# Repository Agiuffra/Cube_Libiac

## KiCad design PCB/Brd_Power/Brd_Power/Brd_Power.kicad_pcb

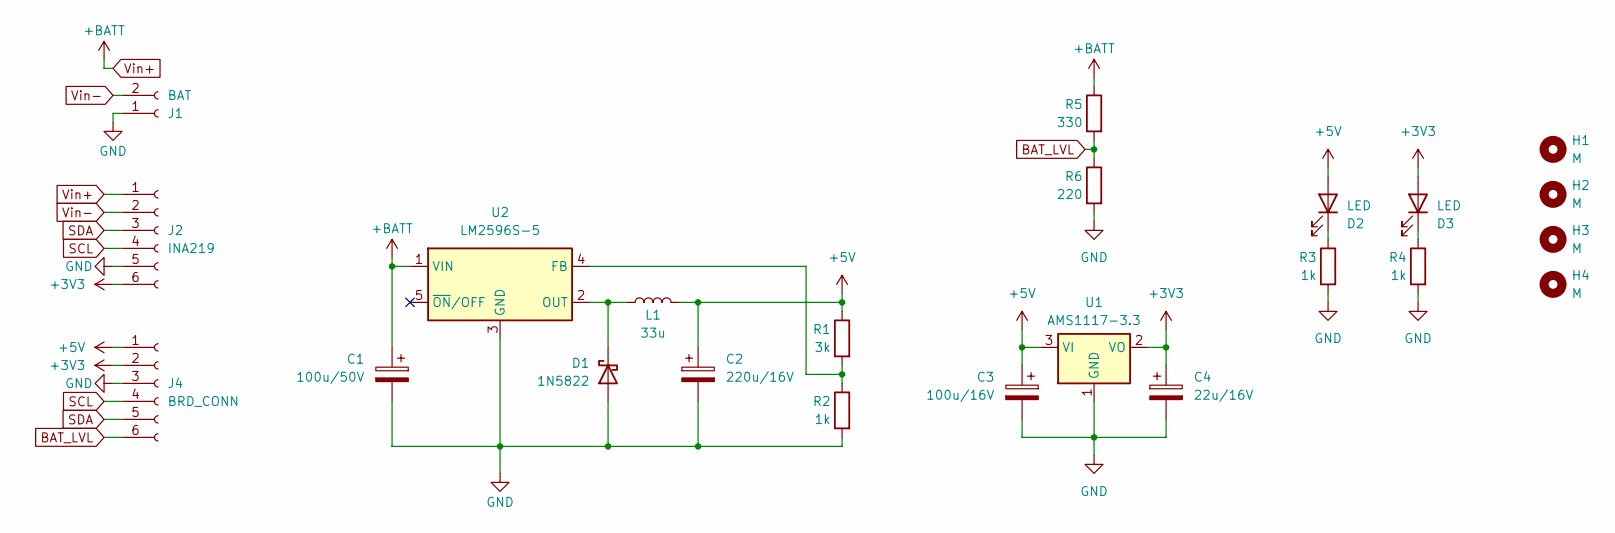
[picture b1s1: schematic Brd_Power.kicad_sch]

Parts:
C1: 100u/50V; CP_Elec_8x5.4
C2: 220u/16V; CP_Elec_8x5.4
C3: 100u/16V; CP_Radial_D6.3mm_P2.50mm
C4: 22u/16V; CP_Radial_D6.3mm_P2.50mm
D1: 1N5822; D_T-1_P5.08mm_Horizontal
D2, D3: LED; LED_D5.0mm_Horizontal_O1.27mm_Z3.0mm
H1, H2, H3, H4: M; MountingHole_3.2mm_M3_ISO14580
J1: BAT; Molex_KK-254_AE-6410-02A_1x02_P2.54mm_Vertical
J2: INA219; PinSocket_1x06_P2.54mm_Vertical
J4: BRD_CONN; PinHeader_1x06_P2.54mm_Vertical
L1: 33u; L_12x12mm_H8mm
R1: 3k; R_Axial_DIN0207_L6.3mm_D2.5mm_P2.54mm_Vertical
R2, R3, R4: 1k; R_Axial_DIN0207_L6.3mm_D2.5mm_P2.54mm_Vertical
R5: 330; R_Axial_DIN0207_L6.3mm_D2.5mm_P2.54mm_Vertical
R6: 220; R_Axial_DIN0207_L6.3mm_D2.5mm_P2.54mm_Vertical
U1: AMS1117-3.3; SOT-223-3_TabPin2
U2: LM2596S-5; TO-263-5_TabPin3

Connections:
+3V3: C4.1, D3.2 (A), J2.6, J4.2, U1.2 (VO)
+5V: C2.1, C3.1, D2.2 (A), J4.1, L1.2, R1.1, U1.3 (VI)
BAT_LVL: J4.6, R5.2, R6.1
GND: C1.2, C2.2, C3.2, C4.2, D1.2 (A), J1.1, J2.5, J4.3, R2.2, R3.2, R4.2, R6.2, U1.1 (GND), U2.3 (GND)
unnamed: D1.1 (K), L1.1, U2.2 (OUT)
unnamed: D2.1 (K), R3.1
unnamed: D3.1 (K), R4.1
unnamed: R1.2, R2.1, U2.4 (FB)
SCL: J2.4, J4.4
SDA: J2.3, J4.5
Vin+: C1.1, J2.1, R5.1, U2.1 (VIN)
Vin-: J1.2, J2.2

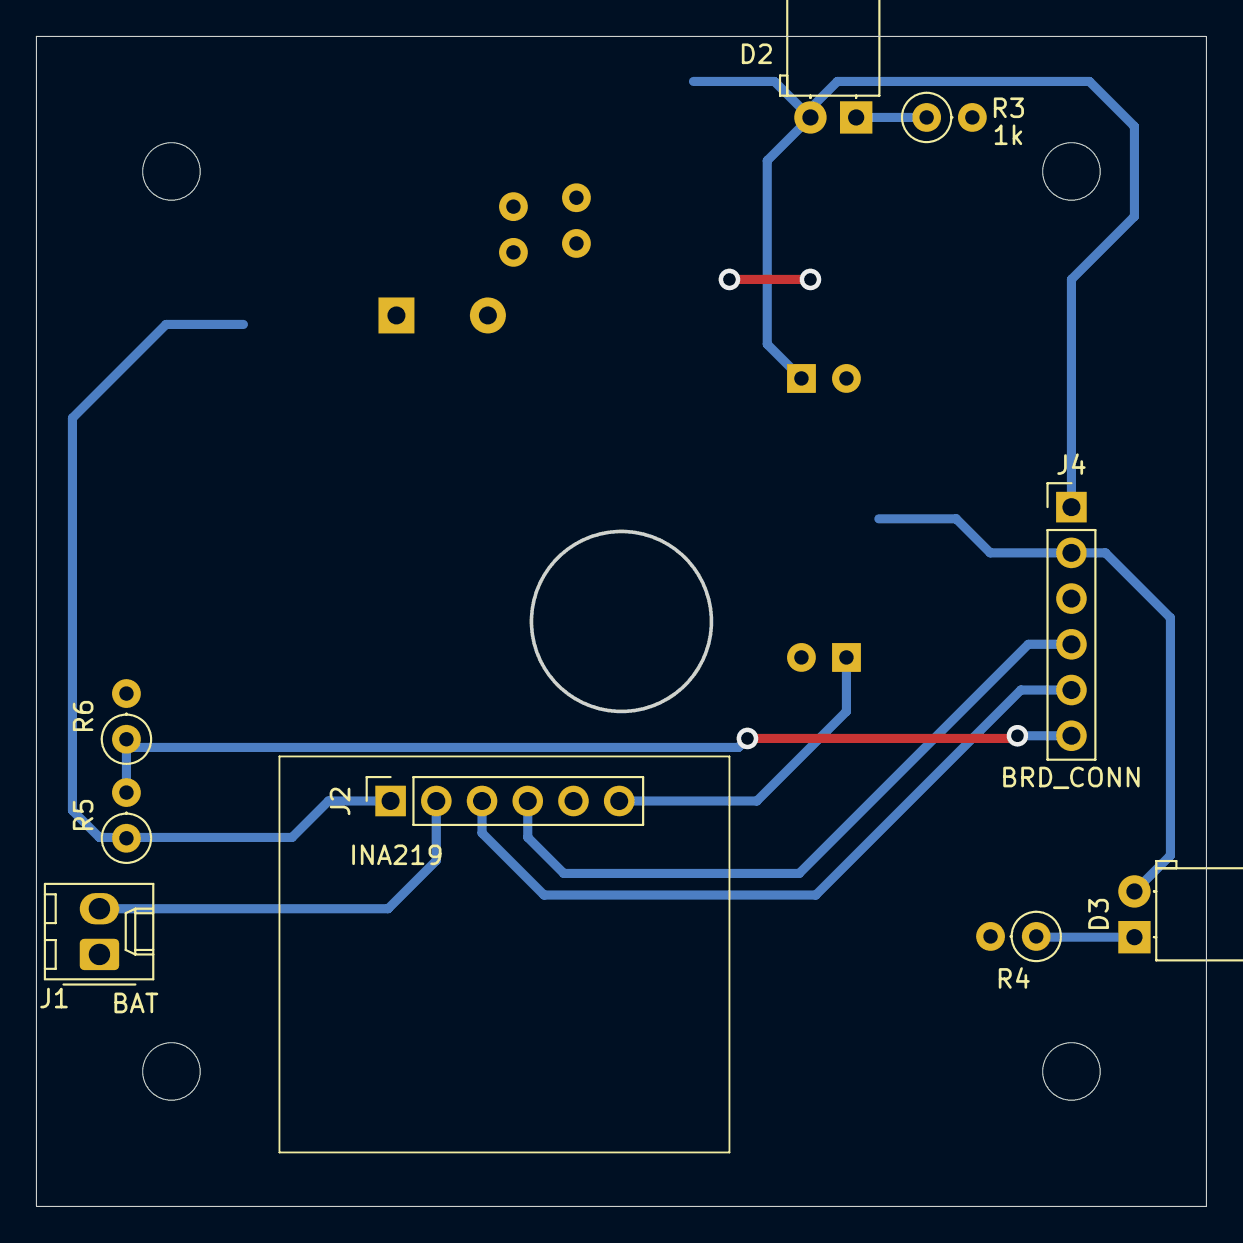
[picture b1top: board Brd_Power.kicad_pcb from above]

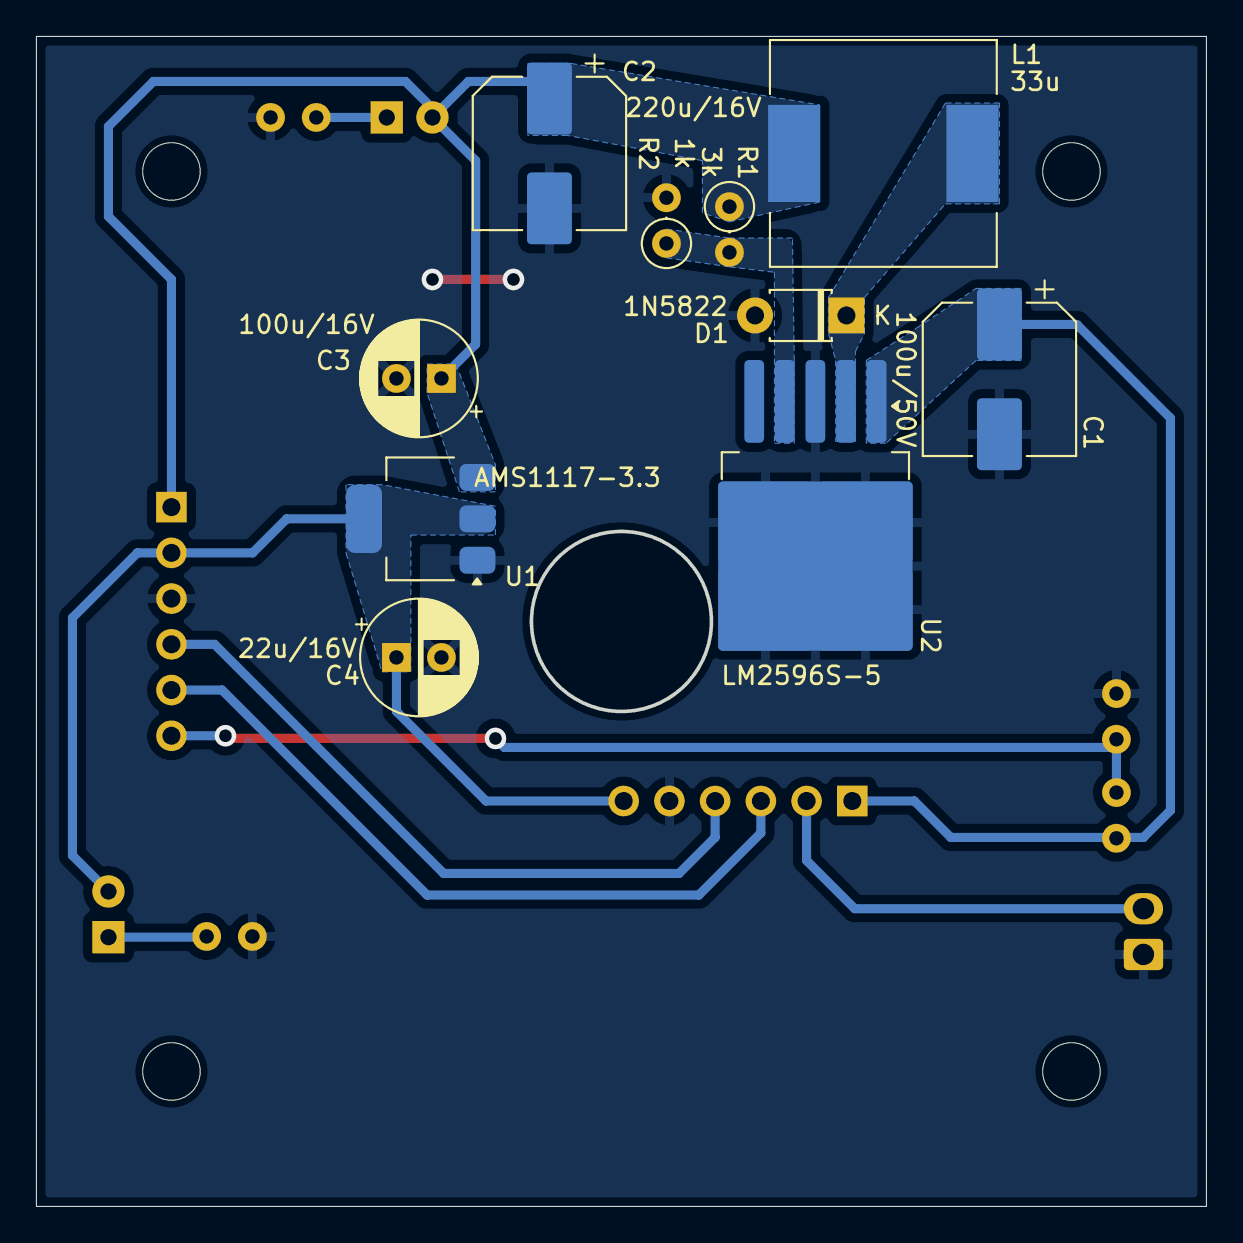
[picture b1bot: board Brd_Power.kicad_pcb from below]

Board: 2 copper layers, 65.0 x 65.0 mm, 23 parts (10 on the bottom side), 12 nets.

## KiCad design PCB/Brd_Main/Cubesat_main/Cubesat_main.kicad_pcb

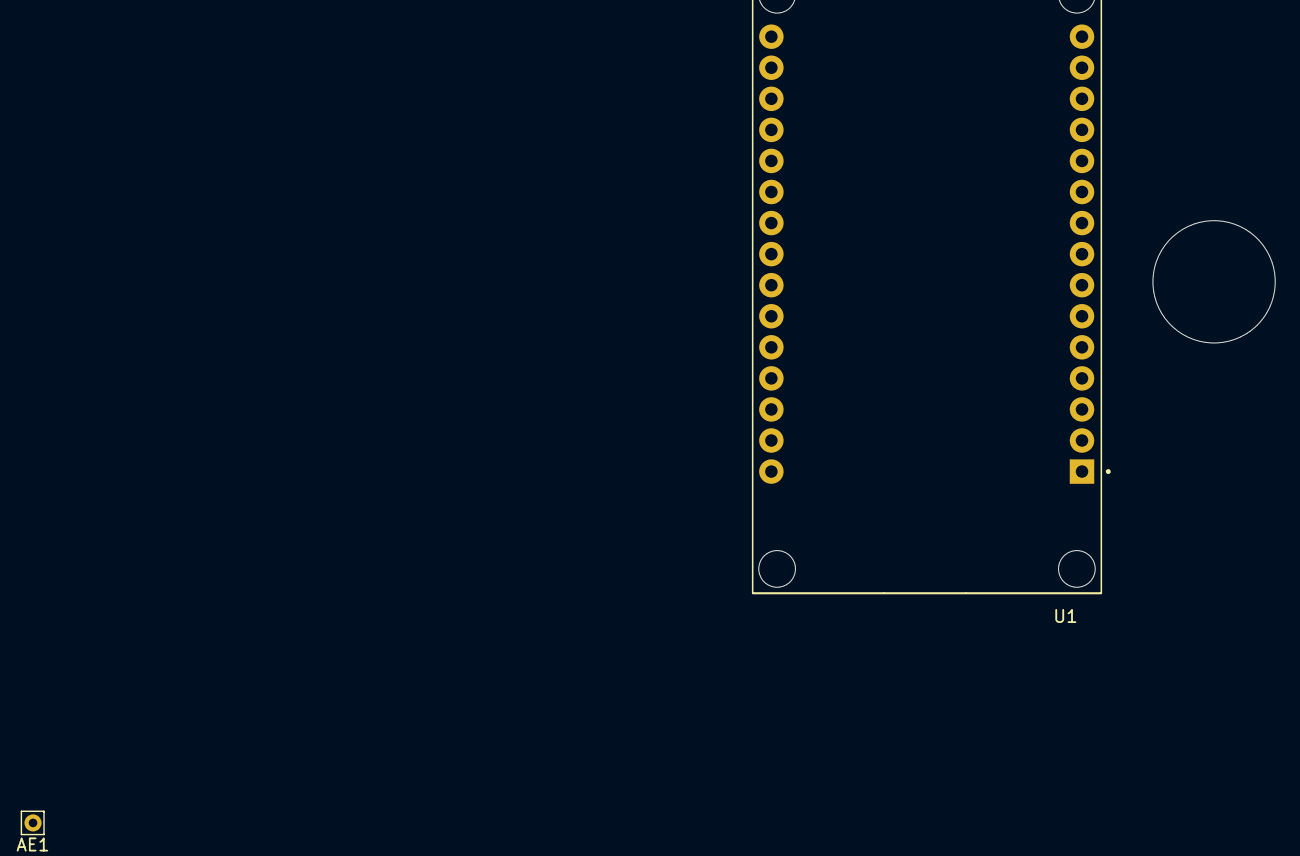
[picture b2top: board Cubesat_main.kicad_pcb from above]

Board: 2 copper layers, 3 parts (1 on the bottom side), 9 nets, no tracks yet.

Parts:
AE1: Antenna; Pin_D0.7mm_L6.5mm_W1.8mm_FlatFork
U1: ESP32-DEVKIT-V1; MODULE_ESP32_DEVKIT_V1
U2: RFM96W; HOPERF_RFM9XW_SMD

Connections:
+3V3: U1.1 (3V3), U2.13 (3.3V)
DIO0: U1.24 (D26), U2.14 (DIO0)
GND: U1.2 (GND), U1.29 (GND), U2.1 (GND), U2.8 (GND), U2.10 (GND)
MISO: U1.27 (D12), U2.2 (MISO)
MOSI: U1.28 (D13), U2.3 (MOSI)
unnamed: AE1.1 (A), U2.9 (ANT)
RST: U1.25 (D27), U2.6 (RESET)
SCK: U1.26 (D14), U2.4 (SCK)
SS: U1.3 (D15), U2.5 (NSS)

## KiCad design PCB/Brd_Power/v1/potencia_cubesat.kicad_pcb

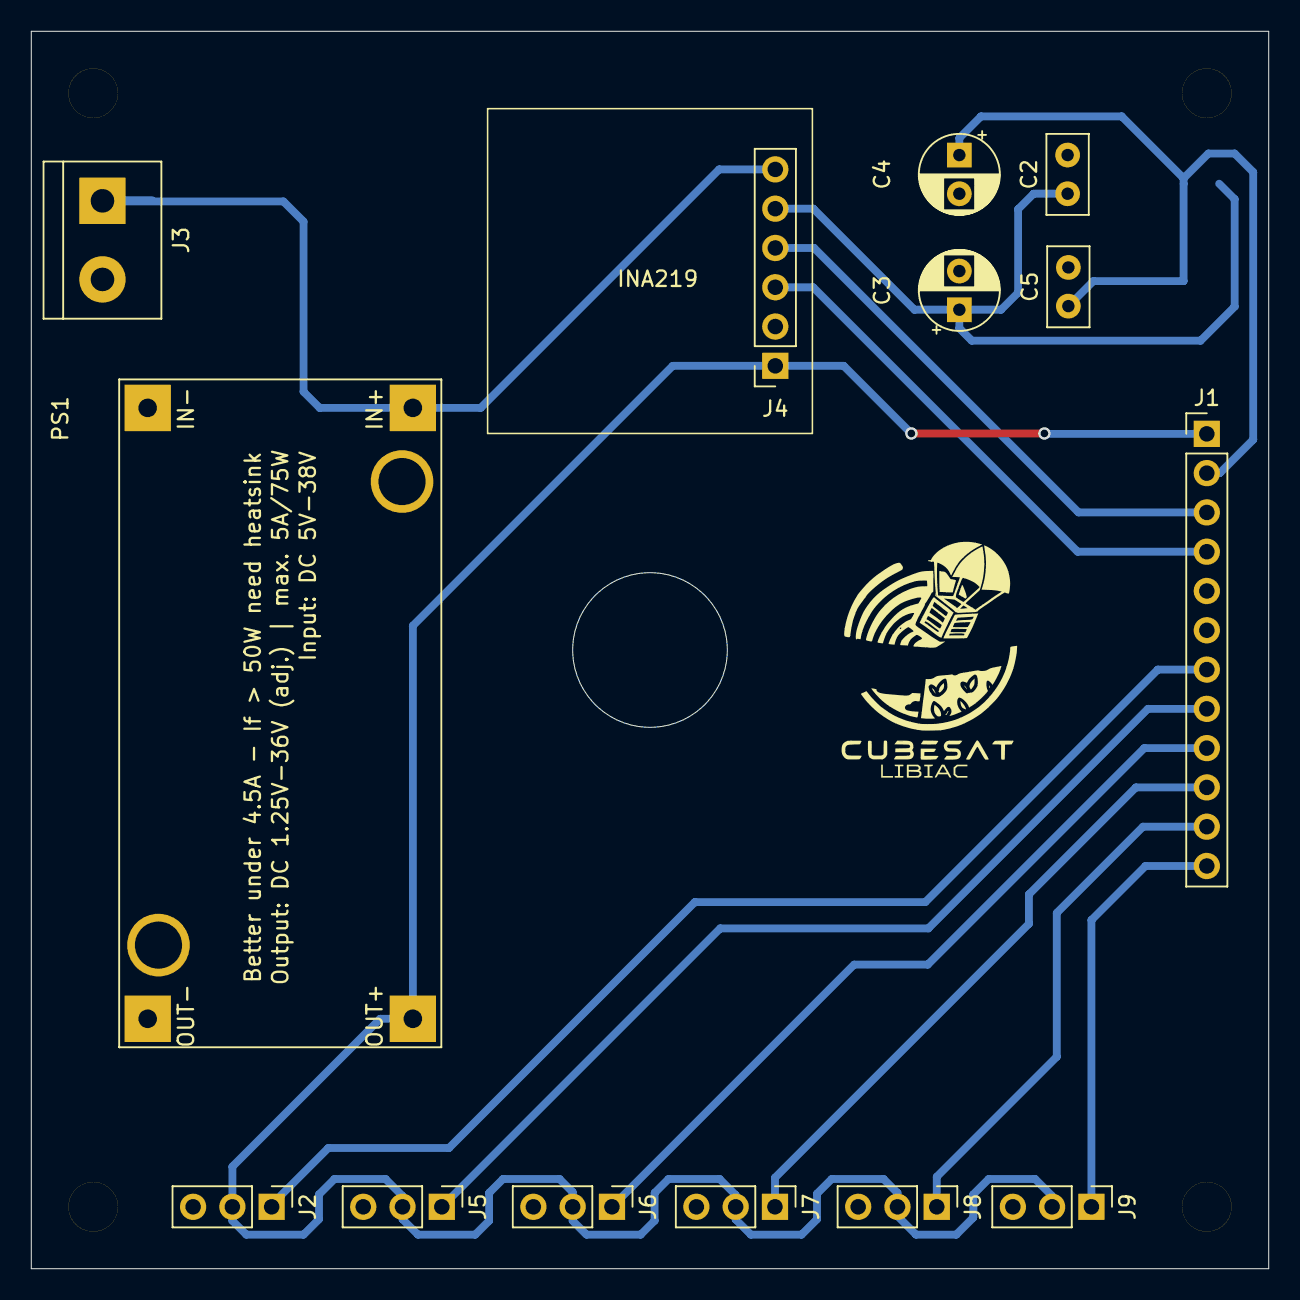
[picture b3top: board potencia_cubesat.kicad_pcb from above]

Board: 2 copper layers, 80.0 x 80.0 mm, 19 parts (1 on the bottom side), 13 nets.

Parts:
C2, C5: 100nF; C_Disc_D5.0mm_W2.5mm_P2.50mm
C3, C4: 10uF; CP_Radial_D5.0mm_P2.50mm
H1: M1; MountingHole_3.2mm_M3_ISO14580
H2: M2; MountingHole_3.2mm_M3_ISO14580
H3: M3; MountingHole_3.2mm_M3_ISO14580
H4: M4; MountingHole_3.2mm_M3_ISO14580
J1: MBoard; PinHeader_1x12_P2.54mm_Vertical
J2: SERVO1; PinHeader_1x03_P2.54mm_Vertical
J3: PWR; TerminalBlock_bornier-2_P5.08mm
J4: INA219; PinSocket_1x06_P2.54mm_Vertical
J5: SERVO2; PinHeader_1x03_P2.54mm_Vertical
J6: SERVO3; PinHeader_1x03_P2.54mm_Vertical
J7: SERVO4; PinHeader_1x03_P2.54mm_Vertical
J8: SERVO5; PinHeader_1x03_P2.54mm_Vertical
J9: SERVO6; PinHeader_1x03_P2.54mm_Vertical
PS1: XL4005_DC-DC
U2: AMS1117; SOT-223-3_TabPin2

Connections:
3.3V: C4.1, C5.1, J1.2, U2.2 (VO)
5V: J1.1, J2.2, J4.1, J5.2, J6.2, J7.2, J8.2, J9.2, PS1.3 (OUT+)
GND: C2.2, C3.2, C4.2, C5.2, J1.5, J1.6, J2.3, J3.2, J4.2, J5.3, J6.3, J7.3, J8.3, J9.3, PS1.2 (IN-), PS1.4 (OUT-), U2.1 (ADJ)
Motor 1: J1.7, J2.1
Motor 2: J1.8, J5.1
Motor 3: J1.9, J6.1
Motor 4: J1.10, J7.1
Motor 5: J1.11, J8.1
Motor 6: J1.12, J9.1
SCL: J1.4, J4.3
SDA: J1.3, J4.4
VIN-: C2.1, C3.1, J4.5, U2.3 (VI)
Vin+: J3.1, J4.6, PS1.1 (IN+)

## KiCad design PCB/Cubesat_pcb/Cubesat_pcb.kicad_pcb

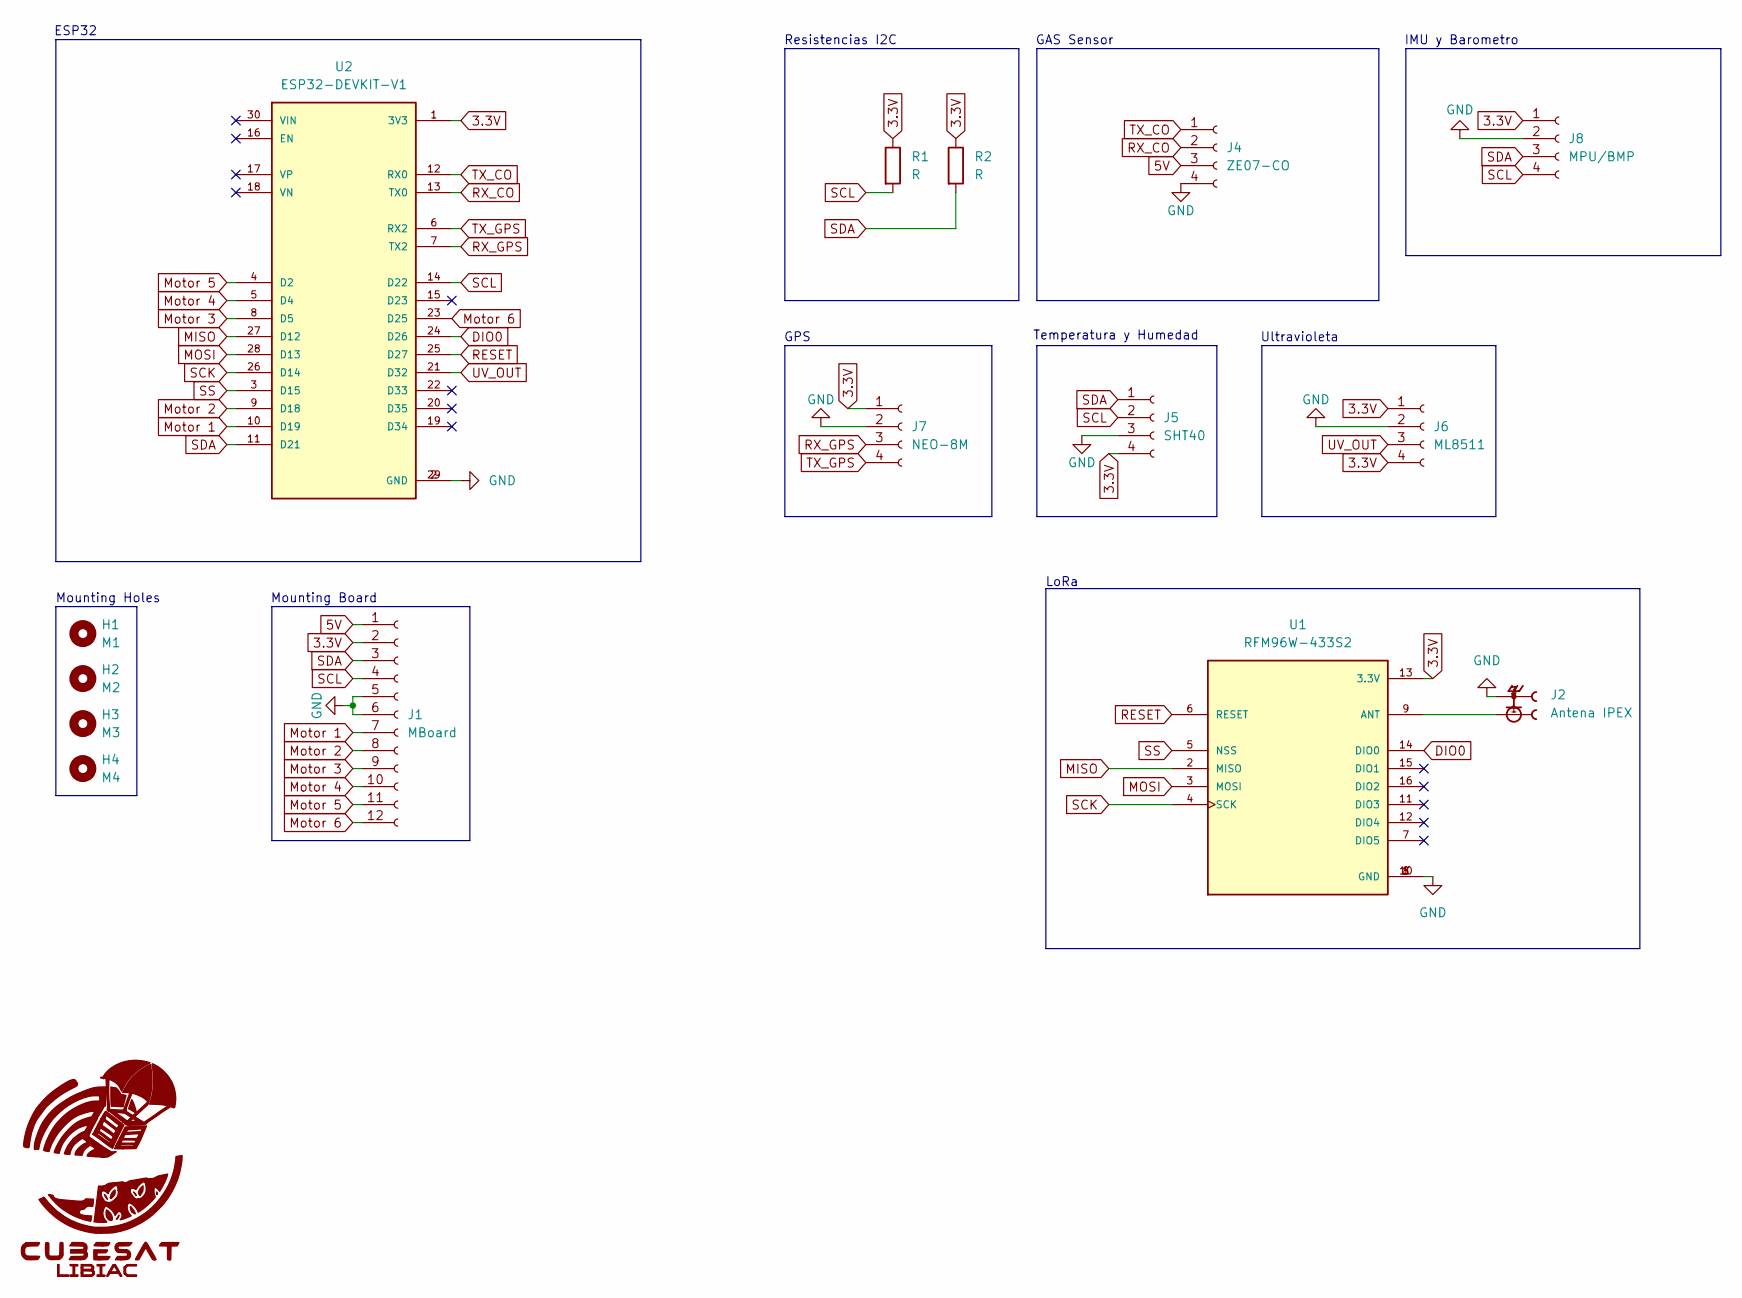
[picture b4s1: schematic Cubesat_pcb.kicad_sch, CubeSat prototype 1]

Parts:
H1: M1; MountingHole_3.2mm_M3_ISO14580
H2: M2; MountingHole_3.2mm_M3_ISO14580
H3: M3; MountingHole_3.2mm_M3_ISO14580
H4: M4; MountingHole_3.2mm_M3_ISO14580
J1: MBoard; PinHeader_1x12_P2.54mm_Vertical
J2: Antena IPEX; IPEX_20279-001E-03; PARTREV 32
J4: ZE07-CO; JST_PH_S4B-PH-K_1x04_P2.00mm_Horizontal
J5: SHT40; JST_PH_S4B-PH-K_1x04_P2.00mm_Horizontal
J6: ML8511; JST_PH_S4B-PH-K_1x04_P2.00mm_Horizontal
J7: NEO-8M; PinSocket_1x04_P2.54mm_Vertical
J8: MPU/BMP; JST_PH_S4B-PH-K_1x04_P2.00mm_Horizontal
R1, R2: R; R_Axial_DIN0204_L3.6mm_D1.6mm_P2.54mm_Vertical
U1: RFM96W-433S2; MODULE_RFM96W-433S2; PARTREV 2.0
U2: ESP32-DEVKIT-V1; MODULE_ESP32_DEVKIT_V1; PARTREV N/A

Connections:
3.3V: J1.2, J5.4, J6.1, J6.4, J7.1, J8.1, R1.1, R2.1, U1.13 (3.3V), U2.1 (3V3)
5V: J1.1, J4.3
DIO0: U1.14 (DIO0), U2.24 (D26)
GND: J1.5, J1.6, J2.2, J2.3, J4.4, J5.3, J6.2, J7.2, J8.2, U1.1 (GND), U1.8 (GND), U1.10 (GND), U2.2 (GND), U2.29 (GND)
MISO: U1.2 (MISO), U2.27 (D12)
MOSI: U1.3 (MOSI), U2.28 (D13)
Motor 1: J1.7, U2.10 (D19)
Motor 2: J1.8, U2.9 (D18)
Motor 3: J1.9, U2.8 (D5)
Motor 4: J1.10, U2.5 (D4)
Motor 5: J1.11, U2.4 (D2)
Motor 6: J1.12, U2.23 (D25)
unnamed: J2.1, U1.9 (ANT)
RESET: U1.6 (RESET), U2.25 (D27)
RX_CO: J4.2, U2.13 (TX0)
RX_GPS: J7.3, U2.7 (TX2)
SCK: U1.4 (SCK), U2.26 (D14)
SCL: J1.4, J5.2, J8.4, R1.2, U2.14 (D22)
SDA: J1.3, J5.1, J8.3, R2.2, U2.11 (D21)
SS: U1.5 (NSS), U2.3 (D15)
TX_CO: J4.1, U2.12 (RX0)
TX_GPS: J7.4, U2.6 (RX2)
UV_OUT: J6.3, U2.21 (D32)

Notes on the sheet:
GPS
Mounting Board
IMU y Barometro
ESP32
Ultravioleta
Mounting Holes
LoRa
Resistencias I2C
GAS Sensor
Temperatura y Humedad

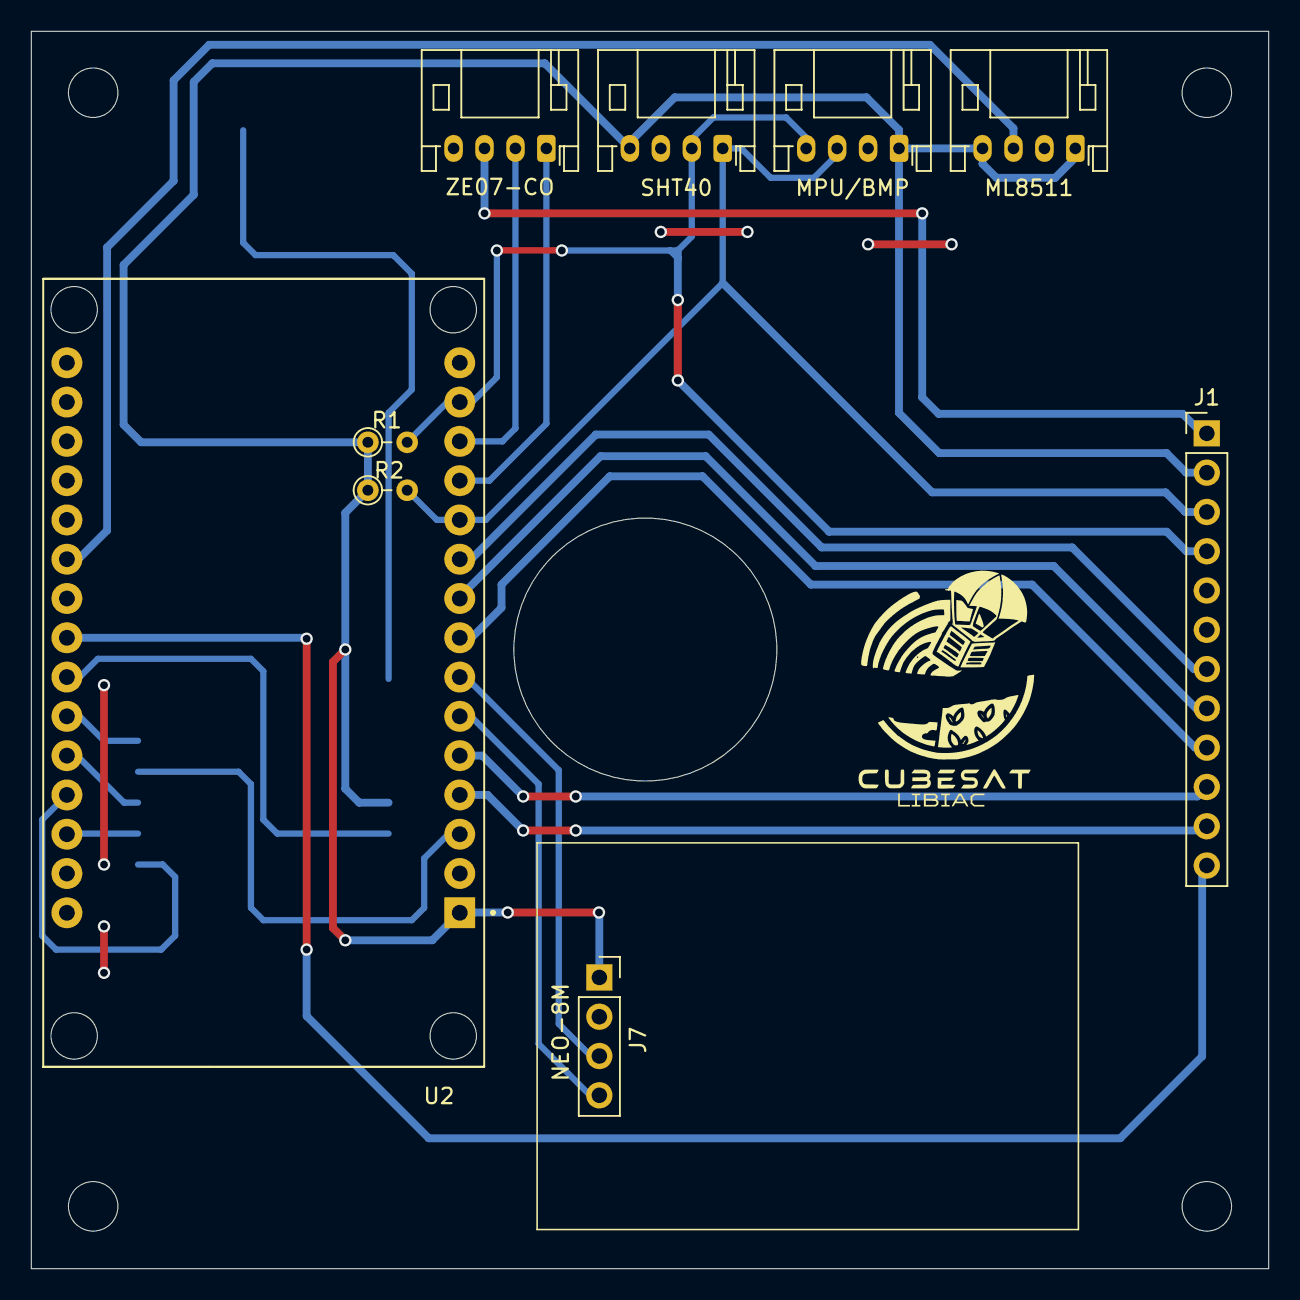
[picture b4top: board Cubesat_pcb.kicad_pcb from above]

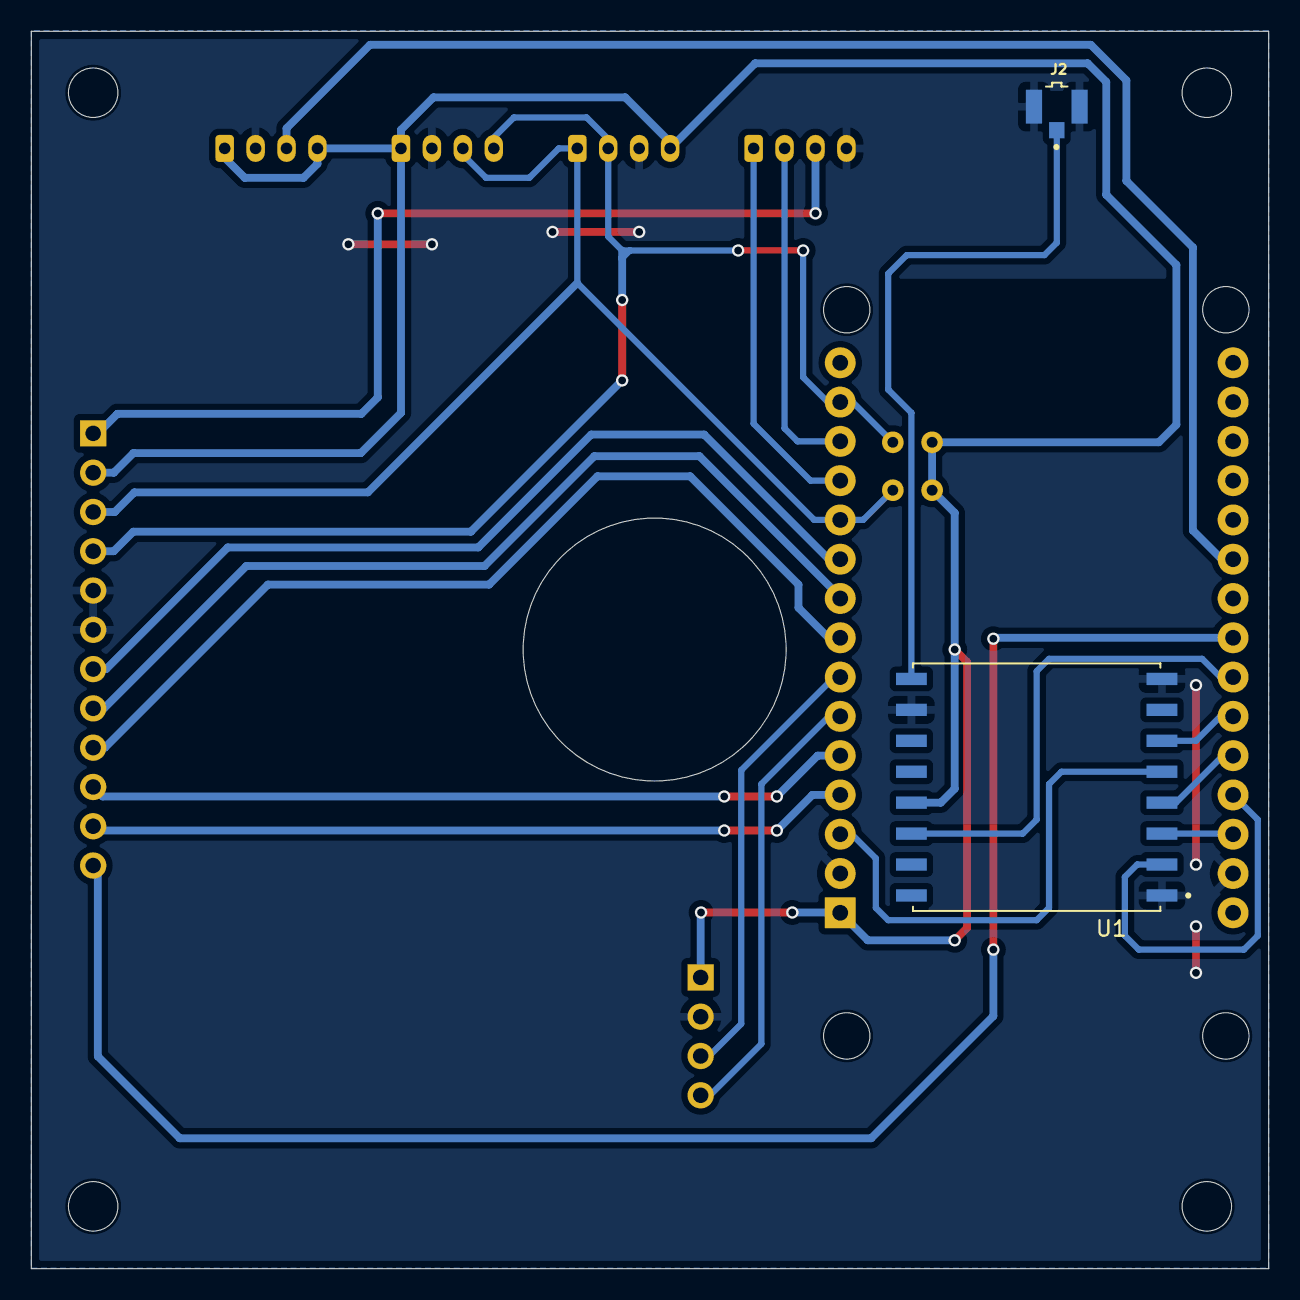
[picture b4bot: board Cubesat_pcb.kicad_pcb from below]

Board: 2 copper layers, 80.0 x 80.0 mm, 15 parts (2 on the bottom side), 23 nets.

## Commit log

2025-01-26 PCB update
2025-01-29 Main PCB Fixed
2025-01-29 PCB POT UPDT
2025-02-17 New PWR BRD
2025-02-18 updt
